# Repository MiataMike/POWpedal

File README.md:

# POWpedal
The design goal of this project is to test Germanium transistors' clipping charactaristics in a guitar pedal that adjusts amplitude and bias for both hard and soft clipping in the same tone.

## Simulations
These simulations use a SPICE-like tool called TINA-TI available for download here: https://www.ti.com/tool/TINA-TI

### TODO
Find the operating conditions (Beta [aka hFE] of transistors and amplitude of guitar pickups) and make sure the gain is adjustable so the quietest combo can still distort and the loudest can play clean

https://github.com/MiataMike/POWpedal/wiki/Transistor-information
http://tomsguitarprojects.blogspot.com/2014/12/electric-guitar-output-voltage-levels.html

## Scope change
Add an oscilloscope using comparators, shift register, an LED driver and an 8x16 LED display (or cooler). An RC oscillator can provide a tunable temporal sampling window (like ms/div). This will be useful for setting the bias and gain, since it will clip unless you have *both* at the right levels. I'll add a bypass so it'll display the upstream signal and act as a cable driver

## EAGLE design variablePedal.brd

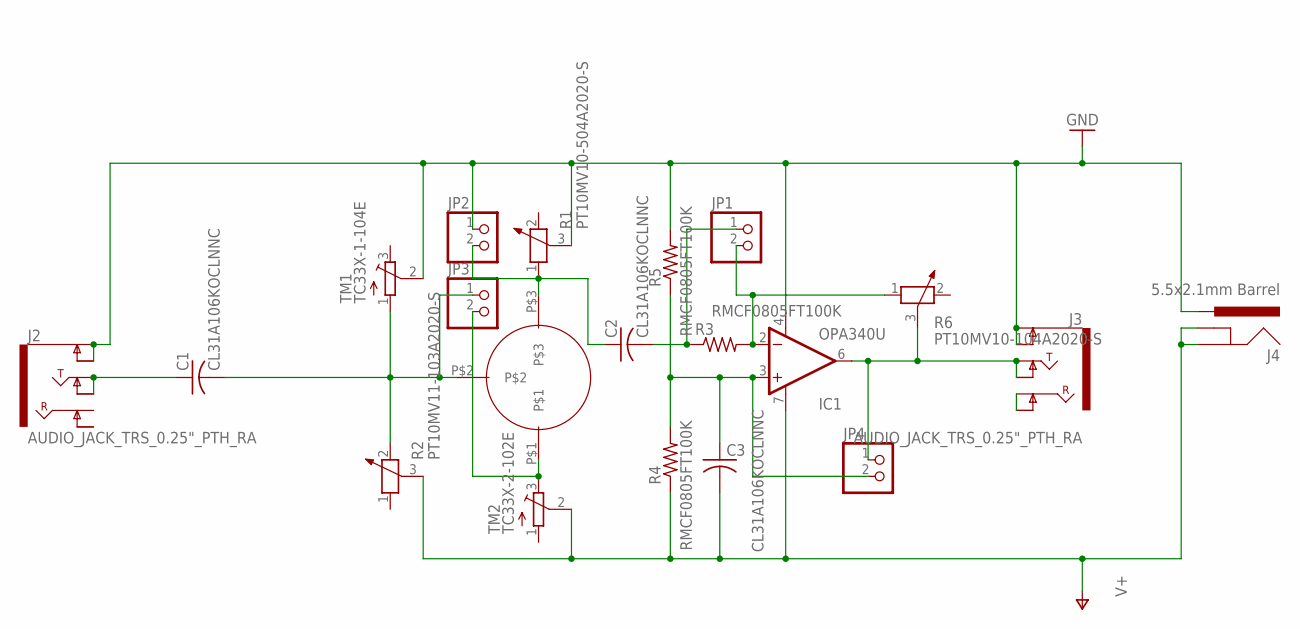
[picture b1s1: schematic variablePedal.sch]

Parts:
C1, C2, C3: CL31A106KOCLNNC; C1206
IC1: OPA340U; SO08
J2, J3: AUDIO_JACK_TRS_0.25"_PTH_RA; AUDIO_JACK_0.25"_TRS_PTH_RA
J4: 5.5x2.1mm Barrel; POWER_JACK_SMD
JP1, JP2, JP3, JP4: PINHD-1X2; 1X02
R1: PT10MV10-504A2020-S; PT-10
R2: PT10MV11-103A2020-S; PT-10
R3, R4, R5: RMCF0805FT100K; R0805
R6: PT10MV10-104A2020-S; PT-10
TM1: TC33X-1-104E; TC33X
TM2: TC33X-2-102E; TC33X
U$1: 917-43-103-41-005000; TO-5

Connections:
GND: IC1.4 (V-), J2.SLEEVE (EARTH), J2.SLEEVE-NORM (EARTH-NORM), J3.SLEEVE (EARTH), J3.SLEEVE-NORM (EARTH-NORM), J4.VIN0 (PWR), JP2.1, R1.3, R5.2, TM1.2 (S)
unnamed: C1.2, JP3.1, R2.2, TM1.1 (A), U$1.P$2
unnamed: C2.1, JP2.2, R1.1, U$1.P$3
unnamed: JP3.2, TM2.3 (E), U$1.P$1
unnamed: C2.2, JP1.1, R3.1
unnamed: C3.1, IC1.3 (+IN), JP4.2, R4.2, R5.1
unnamed: IC1.2 (-IN), JP1.2, R3.2, R6.1
unnamed: IC1.6 (OUT), J3.TIP, J3.TIP-NORM, JP4.1, R6.3
unnamed: J3.RING, J3.RING-NORM
unnamed: C1.1, J2.TIP, J2.TIP-NORM
V+: C3.2, IC1.7 (V+), J4.GND (GNDBREAK), J4.P$4 (GND), R2.3, R4.1, TM2.2 (S)

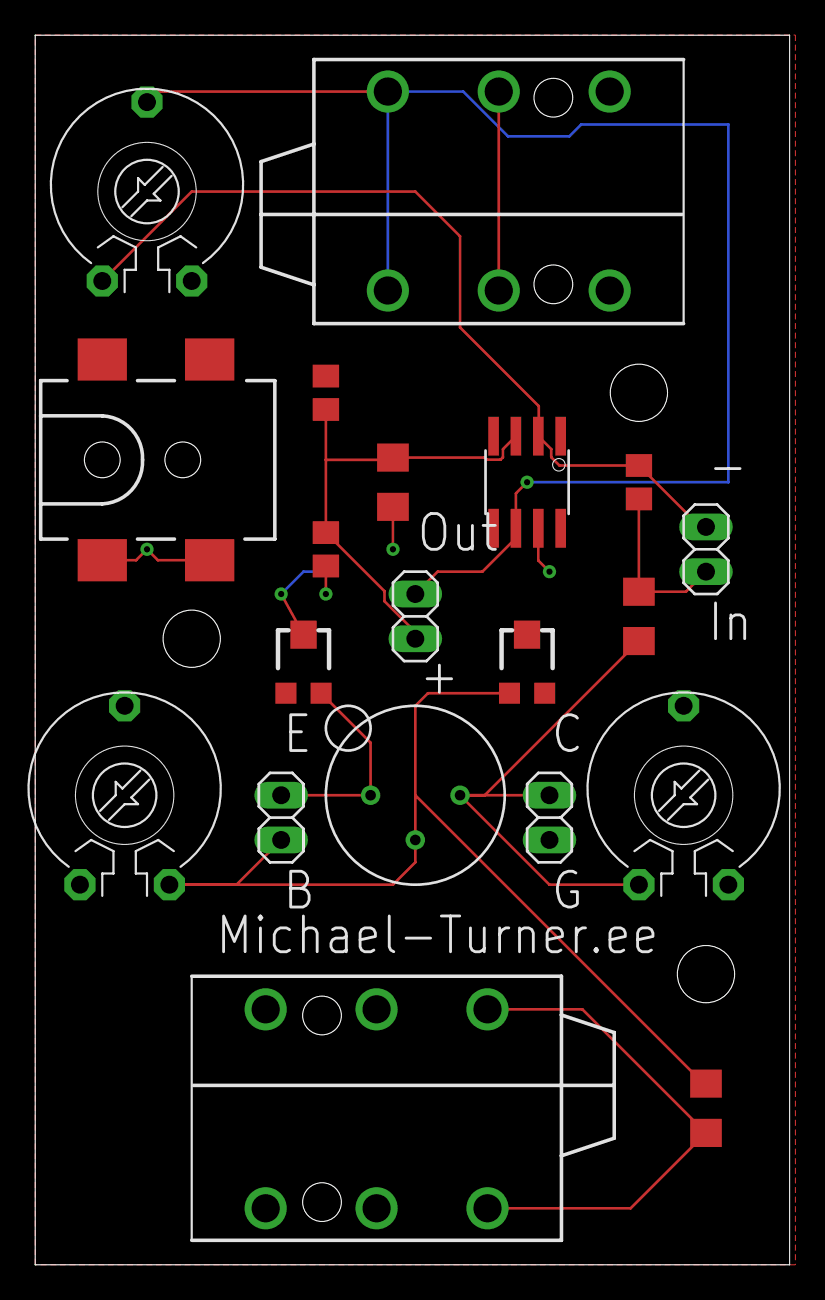
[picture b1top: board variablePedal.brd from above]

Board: 2 copper layers, 42.9 x 69.8 mm, 20 parts (0 on the bottom side), 11 nets.

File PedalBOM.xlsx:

Qty | Value | Device | Package | Parts | Description | Manufacturer | Manufacturer P/N | Digikey
3.0 | 10uF | C-USC1206 | C1206 | C1,C2,C3 | CAPACITOR, American symbol | Samsung Electro-Mechanics | CL31A106KOCLNNC | 1276-2721-1-ND
1.0 | OPA340U | OPA340U | SO08 | IC1 | OpAmp | Texas Instruments | OPA340UA/2K5 | 296-39126-1-ND
DNP | COM-11144 | Audio Jack | Through hole 1/4 TRS Jack | J2,J3 | Horizontal Phono Jack | Sparkfun | COM-11144 | N/A
1.0 | ADC-028-1-T/R-PA10T | Power_Jack SMD | POWER_JACK_SMD | J4 | Barrel Jack connector | Adam tech | ADC-028-1-T/R-PA10T | 2057-ADC-028-1-T/R-PA10TCT-ND
1.0 | 67997-402HLF | PINHD-1X2 | 1X02 | JP1 | Pin Header | Amphenol ICC (FCI) | 67997-402HLF | 609-5502-ND
1.0 | PT10MV10-504A2020-S | POTENTIOMETER_PT-10 | PT-10 | R1 | Potentiometer | Amphenol Piher Sensing Systems | PT10MV10-504A2020-S | 1993-PT10MV10-504A2020-S-ND
1.0 | PT10MV11-103A2020-S | POTENTIOMETER_PT-10 | PT-10 | R2 | Potentiometer | Amphenol Piher Sensing Systems | PT10MV11-103A2020-S | PT10MV11-103A2020-S
3.0 | RMCF0805FT100K | R-US_R0805 | R0805 | R3,R4,R5 | Resistor | Stackpole Electronics Inc | RMCF0805FT100K | RMCF0805FT100KCT-ND
1.0 | PT10MV10-104A2020-S |  | PT-10 | R6 | Potentiometer | Amphenol Piher Sensing Systems | PT10MV10-104A2020-S | 1993-1105-ND
1.0 | TC33X-2-504E | TRIMPOTTC33X | TC33X | TM1 | Trimmer pot | Bourns Inc. | TC33X-2-504E | TC33X-2-504ECT-ND
1.0 | TC33X-1-103E | TRIMPOTTC33X | TC33X | TM2 | Trimmer pot | Bourns Inc. | TC33X-1-103E | TC33X-1-103ECT-ND
1.0 | 917-43-103-41-005000 | 917-43-103-41-005000 | TO-5 | U$1 | TO-5 Socket | Mill-Max Manufacturing Corp. | 917-43-103-41-005000 | ED90273-ND

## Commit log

2021-03-07 Simulation files
    Working out how the pedal should operate in simulation. The goal here is to have both a hard and soft clipping, which should really show off the transistor behavior
2021-03-22 Starting schematic capture
2021-03-22 Parts selected and placed (values TBD)
2021-03-22 Routed nets, ERC indicates no values
2021-03-22 adding board
2021-03-22 parts placed
2021-03-22 Passes DRC with no errors, however, BJT holder TBD
2021-03-22 Some finishing touches (labels, tidy placement)
2021-03-22 Revert "Some finishing touches (labels, tidy placement)"
    This reverts commit a6e963cb4720da940ed62cc4250a87c95adb02c4.
2021-03-27 Added 2N32 datasheet pictures
2021-03-27 Added Datasheet directory
2021-04-25 fixed trace collision
2021-05-28 Updated schematic with socket, created BOM and Gerbers
2021-06-08 added probe points, mounting holes and ordered!

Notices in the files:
parts and their libraries:
SparkFun-Connectors: Licensing: Creative Commons ShareAlike 4.0 International - https://creativecommons.org/licenses/by-sa/4.0
